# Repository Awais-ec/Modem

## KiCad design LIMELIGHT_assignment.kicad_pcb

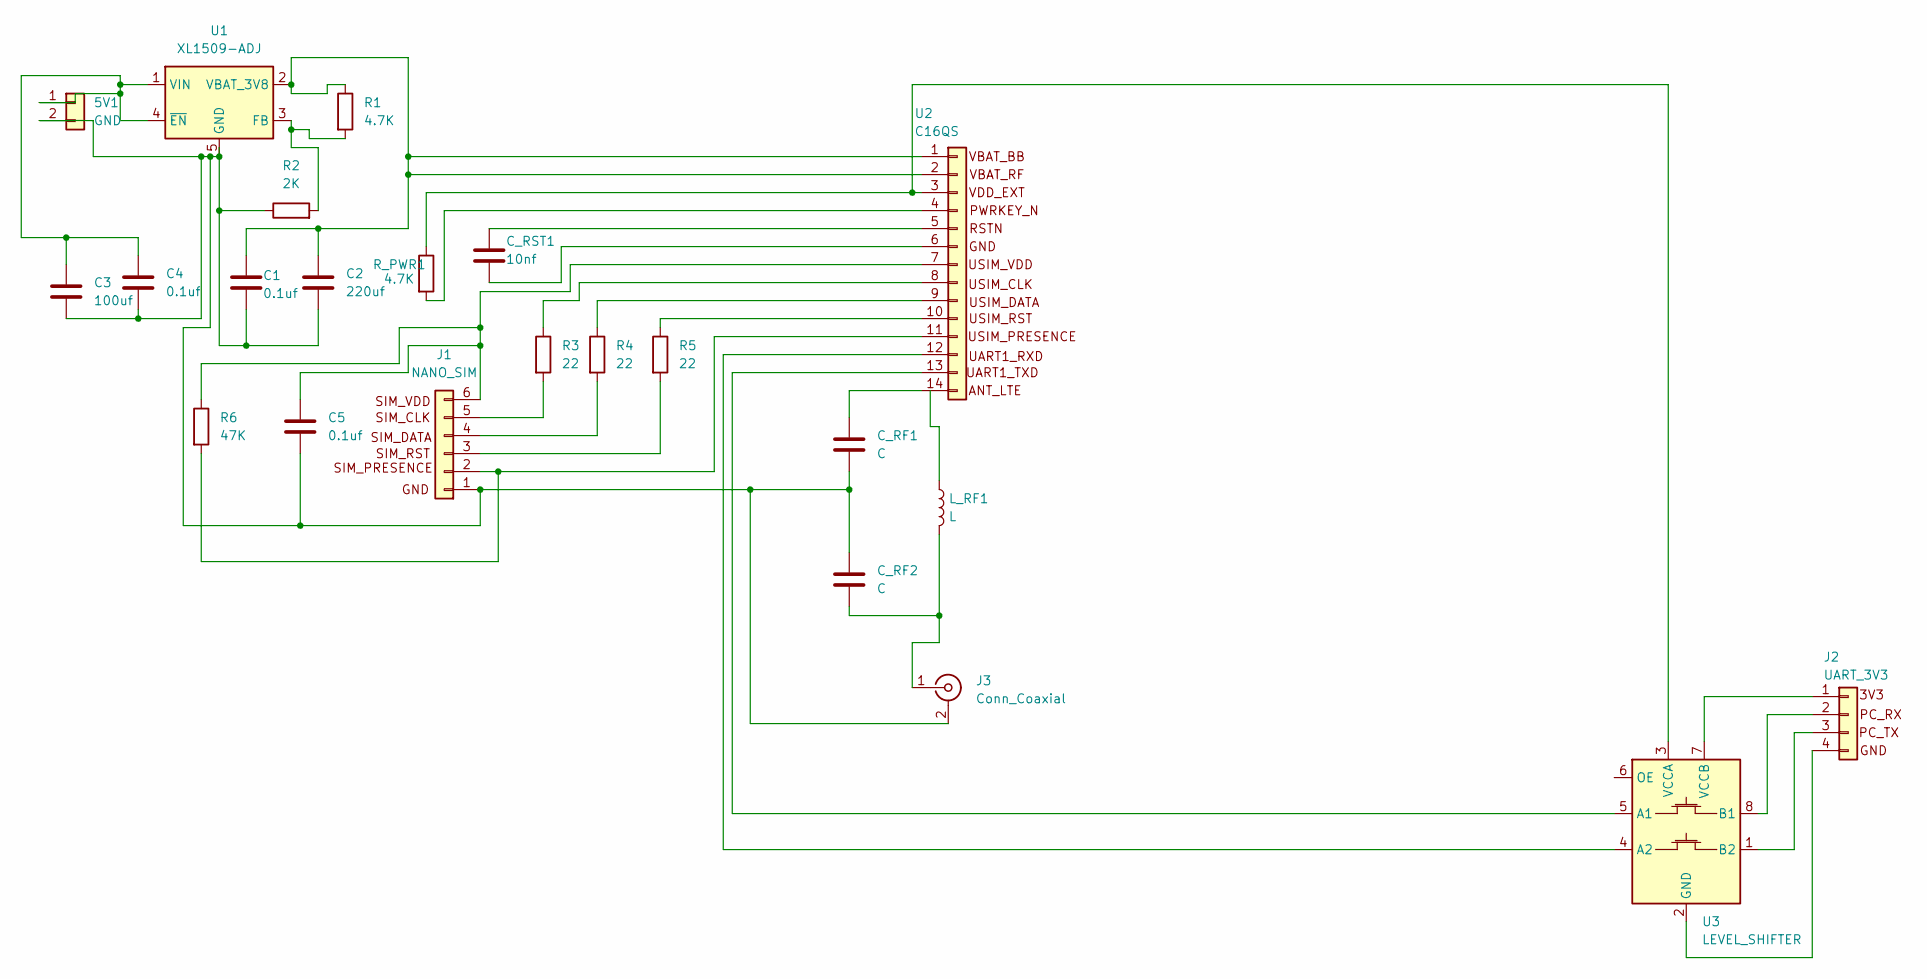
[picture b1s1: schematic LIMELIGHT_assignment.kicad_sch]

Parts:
5V1: GND; Molex_KK-254_AE-6410-02A_1x02_P2.54mm_Vertical
C1, C4, C5: 0.1uf; C_0201_0603Metric
C2: 220uf; C_0201_0603Metric
C3: 100uf; C_0201_0603Metric
C_RF1, C_RF2: C; C_0201_0603Metric
C_RST1: 10nf; C_0201_0603Metric
J1: NANO_SIM; Molex_KK-396_5273-06A_1x06_P3.96mm_Vertical
J2: UART_3V3; Molex_KK-254_AE-6410-04A_1x04_P2.54mm_Vertical
J3: Conn_Coaxial; BNC_Amphenol_031-5539_Vertical
L_RF1: L; L_6.3x6.3_H3
R1: 4.7K; R_0603_1608Metric
R2: 2K; R_0603_1608Metric
R3, R4, R5: 22; R_0603_1608Metric
R6: 47K; R_0603_1608Metric
R_PWR1: 4.7K; R_0603_1608Metric
U1: XL1509-ADJ; SOIC-8_3.9x4.9mm_P1.27mm
U2: C16QS; Molex_KK-254_AE-6410-14A_1x14_P2.54mm_Vertical
U3: LEVEL_SHIFTER; SSOP-8_2.95x2.8mm_P0.65mm

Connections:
unnamed: 5V1.1, C3.1, C4.1, U1.1 (VIN), U1.4 (~EN)
unnamed: 5V1.2, C1.2, C2.2, C3.2, C4.2, C5.2, C_RF1.2, C_RF2.1, J1.1, J3.2 (Ext), R2.1, U1.5 (GND), U1.6 (GND), U1.7 (GND), U1.8 (GND)
unnamed: J1.2, R6.2, U2.11
unnamed: J1.3, R5.2
unnamed: J1.4, R4.2
unnamed: J1.5, R3.2
unnamed: C5.1, J1.6, R6.1, U2.7
unnamed: J2.1, U3.7 (VCCB)
unnamed: J2.2, U3.8 (B1)
unnamed: J2.3, U3.1 (B2)
unnamed: J2.4, U3.2 (GND)
unnamed: C_RF2.2, J3.1 (In), L_RF1.2
unnamed: R1.2, R2.2, U1.3 (FB)
unnamed: C1.1, C2.1, R1.1, U1.2 (VBAT_3V8), U2.1, U2.2
unnamed: R_PWR1.1, U2.3, U3.3 (VCCA)
unnamed: R_PWR1.2, U2.4
unnamed: C_RST1.1, U2.5
unnamed: C_RST1.2, U2.6
unnamed: R3.1, U2.8
unnamed: R4.1, U2.9
unnamed: R5.1, U2.10
unnamed: U2.12, U3.4 (A2)
unnamed: U2.13, U3.5 (A1)
unnamed: C_RF1.1, U2.14

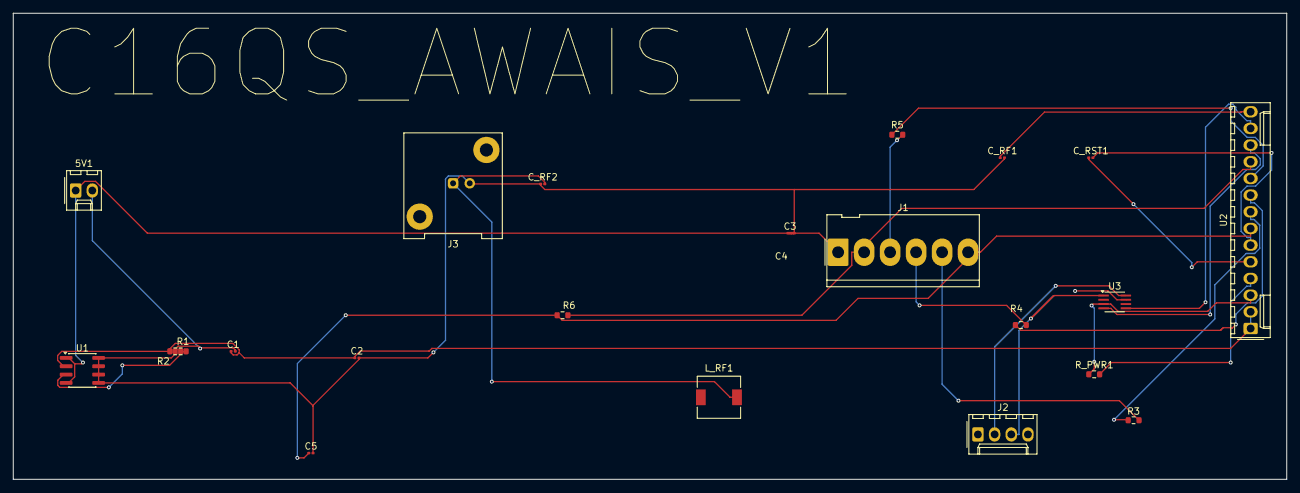
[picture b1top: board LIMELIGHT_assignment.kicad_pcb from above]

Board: 2 copper layers, 194.0 x 71.0 mm, 23 parts (0 on the bottom side), 24 nets.
